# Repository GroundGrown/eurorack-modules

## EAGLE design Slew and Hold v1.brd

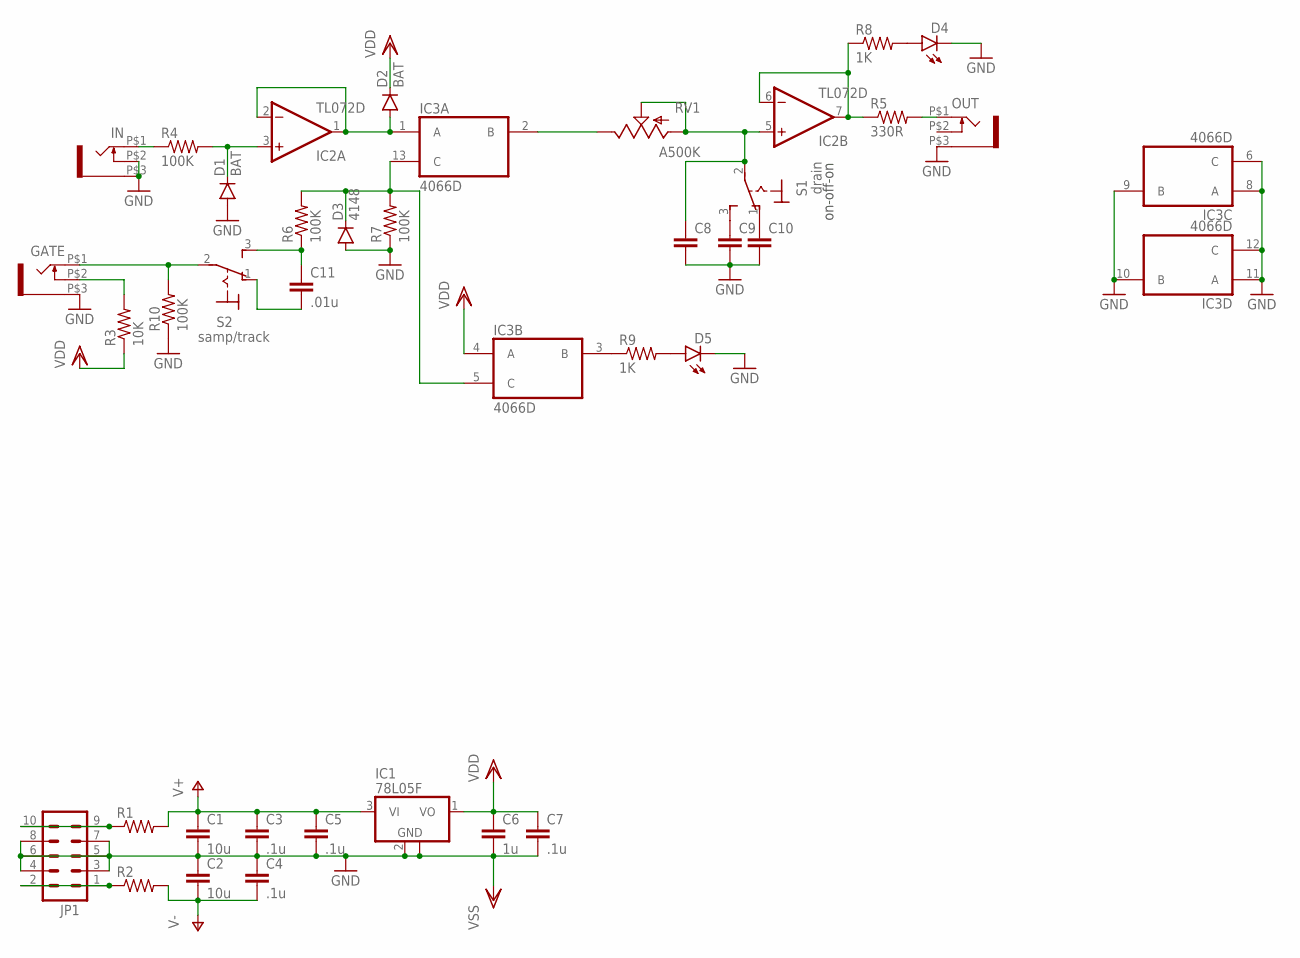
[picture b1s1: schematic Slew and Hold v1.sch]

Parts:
C1, C2: 10u; 1206
C3, C4, C5, C7: .1u; 0805
C6: 1u; 0805
C8, C9, C10: CAP0805; 0805
C11: .01u; 0805
D1, D2: BAT; SOD-123
D3: 4148; SOD-123
D4, D5: LED3MM
GATE: WQP-PJ301M-12_JACK
IC1: 78L05F; SOT89
IC2: TL072D; SO08
IC3: 4066D; SO14
IN: WQP-PJ301M-12_JACK
JP1: M05X2PTH; AVR_ICSP
OUT: WQP-PJ301M-12_JACK
R1, R2: RESISTOR0805-RES; 0805
R3: 10K; 0805
R4, R6, R7, R10: 100K; 0805
R5: 330R; 0805
R8, R9: 1K; 0805
RV1: A500K; ALPS_POT
S1: drain; M9040P
S2: samp/track; M9040P

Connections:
GND: C1.2, C2.1, C3.2, C4.1, C5.2, C6.2, C7.2, C8.2, C9.2, C10.2, D1.A, D3.A, D4.K (C), D5.K (C), GATE.P$3 (1), IC1.2 (GND), IC1.2@1 (GND), IC3.6 (C), IC3.7 (VSS), IC3.8 (A), IC3.9 (B), IC3.10 (B), IC3.11 (A), IC3.12 (C), IN.P$2 (3), IN.P$3 (1), JP1.3, JP1.4, JP1.5, JP1.6, JP1.7, JP1.8, OUT.P$3 (1), R7.1, R10.1
unnamed: JP1.9, JP1.10, R1.1
unnamed: JP1.1, JP1.2, R2.1
unnamed: D2.A, IC2.1 (OUT), IC2.2 (-IN), IC3.1 (A)
unnamed: D1.C, IC2.3 (+IN), R4.2
unnamed: IN.P$1 (2), R4.1
unnamed: IC3.2 (B), RV1.P$1 (E)
unnamed: C8.1, IC2.5 (+IN), RV1.P$2 (S), RV1.P$3 (A), S1.2
unnamed: C9.1, S1.3 (S)
unnamed: C10.1, S1.1 (O)
unnamed: D4.A, R8.2
unnamed: IC2.6 (-IN), IC2.7 (OUT), R5.1, R8.1
unnamed: GATE.P$1 (2), R10.2, S2.2
unnamed: D3.C, IC3.5 (C), IC3.13 (C), R6.2, R7.2
unnamed: GATE.P$2 (3), R3.2
unnamed: OUT.P$1 (2), R5.2
unnamed: C11.1, R6.1, S2.3 (S)
unnamed: C11.2, S2.1 (O)
unnamed: IC3.3 (B), R9.1
unnamed: D5.A, R9.2
V+: C1.1, C3.1, C5.1, IC1.3 (VI), IC2.8 (V+), R1.2
V-: C2.2, C4.2, IC2.4 (V-), R2.2
VDD: C6.1, C7.1, D2.C, IC1.1 (VO), IC3.4 (A), IC3.14 (VDD), R3.1

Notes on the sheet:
on-off-on

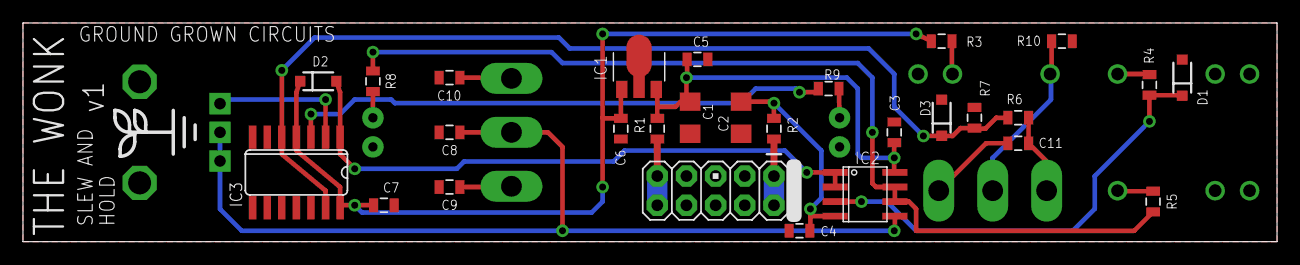
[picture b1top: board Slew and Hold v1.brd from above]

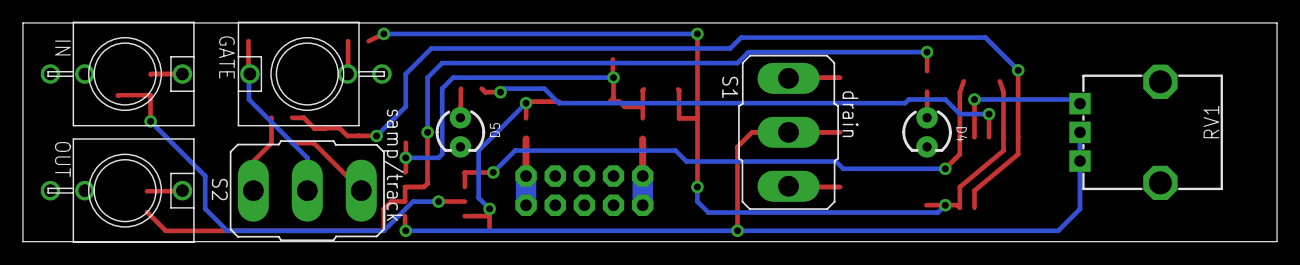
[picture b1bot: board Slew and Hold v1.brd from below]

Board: 2 copper layers, 109.2 x 19.1 mm, 37 parts (8 on the bottom side), 23 nets.

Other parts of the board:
U$1: LOGO_SMALL

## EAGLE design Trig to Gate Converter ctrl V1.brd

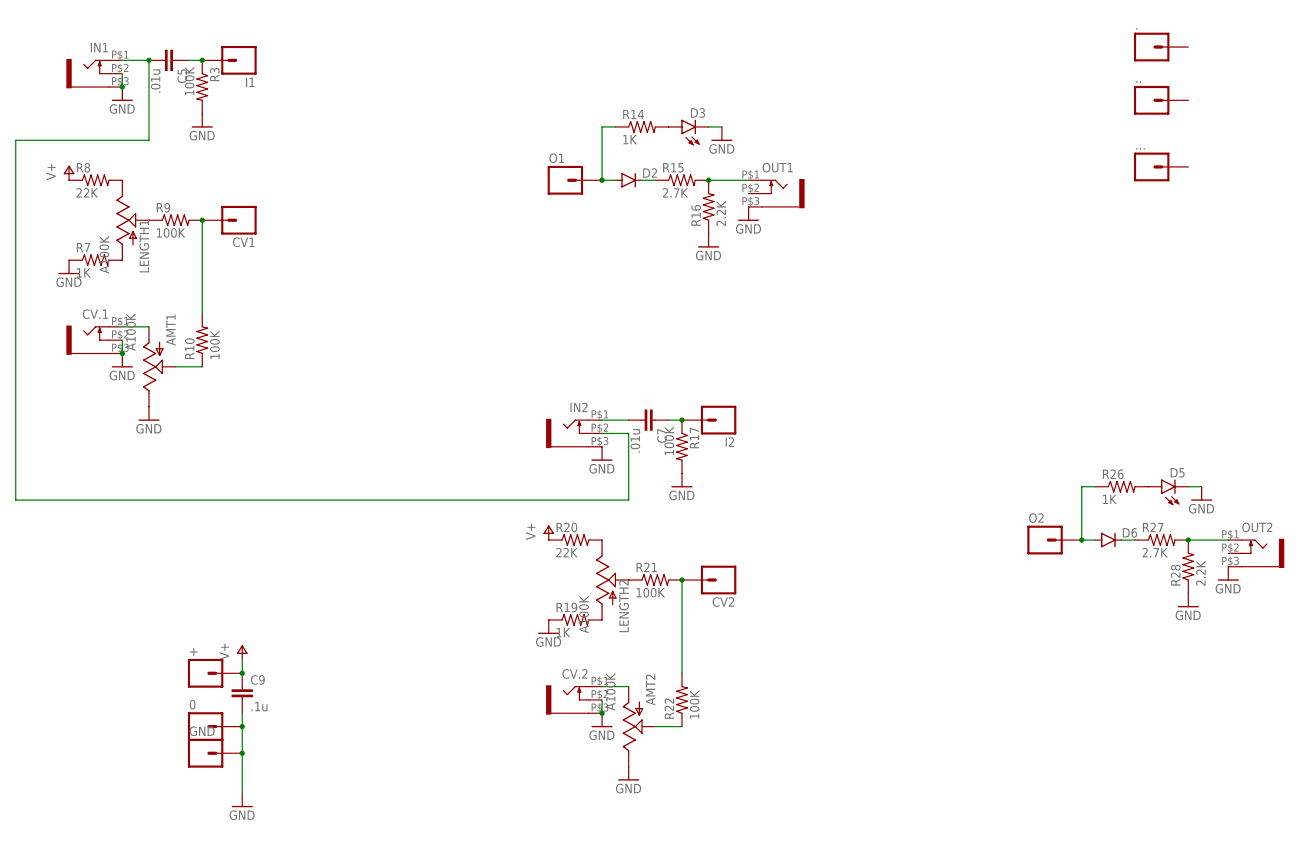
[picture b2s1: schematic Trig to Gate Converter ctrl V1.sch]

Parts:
0, ., .., ...: M01PTH; 1X01
+: M01PTH; 1X01
AMT1, AMT2: A100K; ALPS_POT
C5, C7: .01u; 0805
C9: .1u; 0805
CV1, CV2: M01PTH; 1X01
CV.1, CV.2: WQP-PJ301M-12_JACK
D2, D6: DIODESOD123; SOD-123
D3, D5: LED3MM
GND: M01PTH; 1X01
I1, I2: M01PTH; 1X01
IN1, IN2: WQP-PJ301M-12_JACK
LENGTH1, LENGTH2: A100K; ALPS_POT
O1, O2: M01PTH; 1X01
OUT1, OUT2: WQP-PJ301M-12_JACK
R3, R9, R10, R17, R21, R22: 100K; 0805
R7, R14, R19, R26: 1K; 0805
R8, R20: 22K; 0805
R15, R27: 2.7K; 0805
R16, R28: 2.2K; 0805

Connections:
GND: 0.1, AMT1.P$1 (E), AMT2.P$1 (E), C9.2, CV.1.P$2 (3), CV.1.P$3 (1), CV.2.P$2 (3), CV.2.P$3 (1), D3.K (C), D5.K (C), GND.1, IN1.P$2 (3), IN1.P$3 (1), IN2.P$3 (1), OUT1.P$3 (1), OUT2.P$3 (1), R3.2, R7.1, R16.1, R17.2, R19.1, R28.1
unnamed: LENGTH2.P$1 (E), R20.2
unnamed: LENGTH1.P$3 (A), R7.2
unnamed: LENGTH1.P$1 (E), R8.2
unnamed: LENGTH1.P$2 (S), R9.1
unnamed: AMT1.P$3 (A), CV.1.P$1 (2)
unnamed: AMT1.P$2 (S), R10.1
unnamed: CV1.1, R9.2, R10.2
unnamed: C5.2, IN1.P$1 (2), IN2.P$2 (3)
unnamed: C5.1, I1.1, R3.1
unnamed: D3.A, R14.2
unnamed: OUT1.P$1 (2), R15.2, R16.2
unnamed: D2.C, R15.1
unnamed: D2.A, O1.1, R14.1
unnamed: LENGTH2.P$3 (A), R19.2
unnamed: LENGTH2.P$2 (S), R21.1
unnamed: AMT2.P$3 (A), CV.2.P$1 (2)
unnamed: AMT2.P$2 (S), R22.1
unnamed: CV2.1, R21.2, R22.2
unnamed: C7.2, IN2.P$1 (2)
unnamed: C7.1, I2.1, R17.1
unnamed: D5.A, R26.2
unnamed: OUT2.P$1 (2), R27.2, R28.2
unnamed: D6.C, R27.1
unnamed: D6.A, O2.1, R26.1
V+: +.1, C9.1, R8.1, R20.1

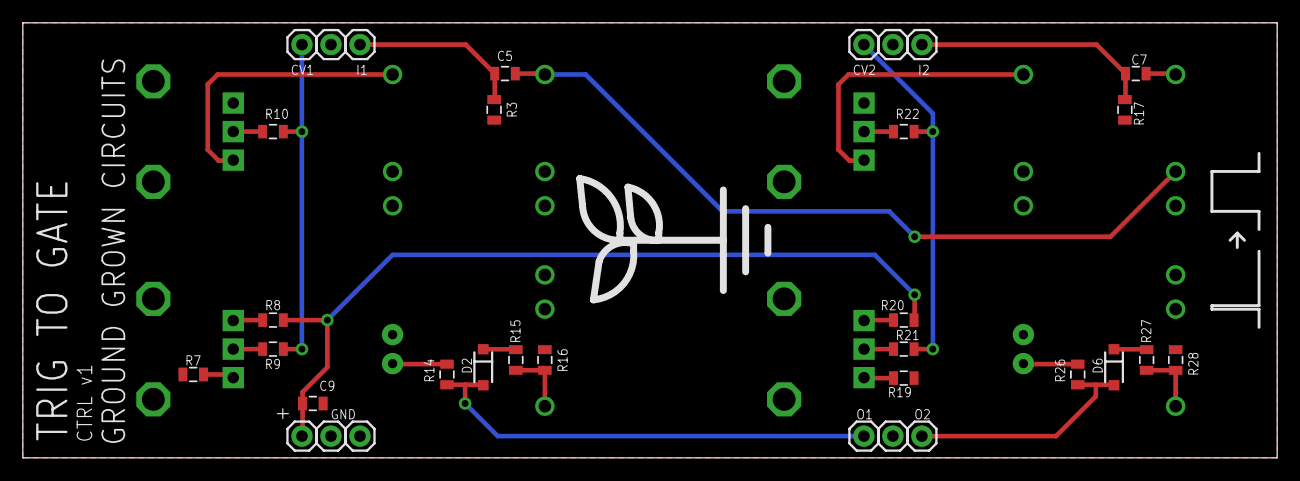
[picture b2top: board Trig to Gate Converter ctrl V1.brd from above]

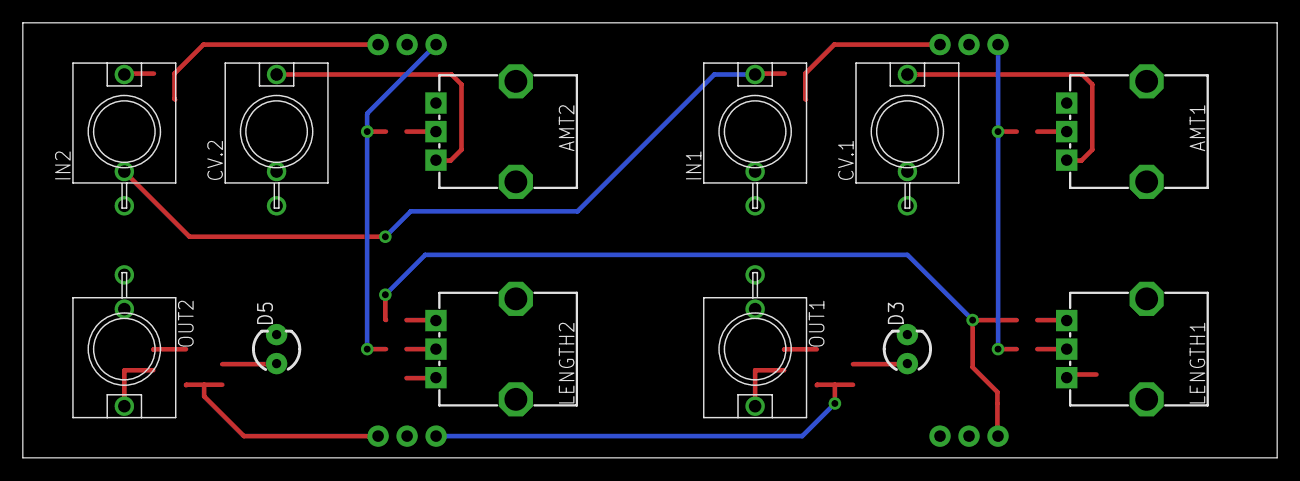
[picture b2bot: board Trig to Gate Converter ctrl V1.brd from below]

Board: 2 copper layers, 109.9 x 38.1 mm, 46 parts (12 on the bottom side), 26 nets.

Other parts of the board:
U$1: LOGO_LARGE

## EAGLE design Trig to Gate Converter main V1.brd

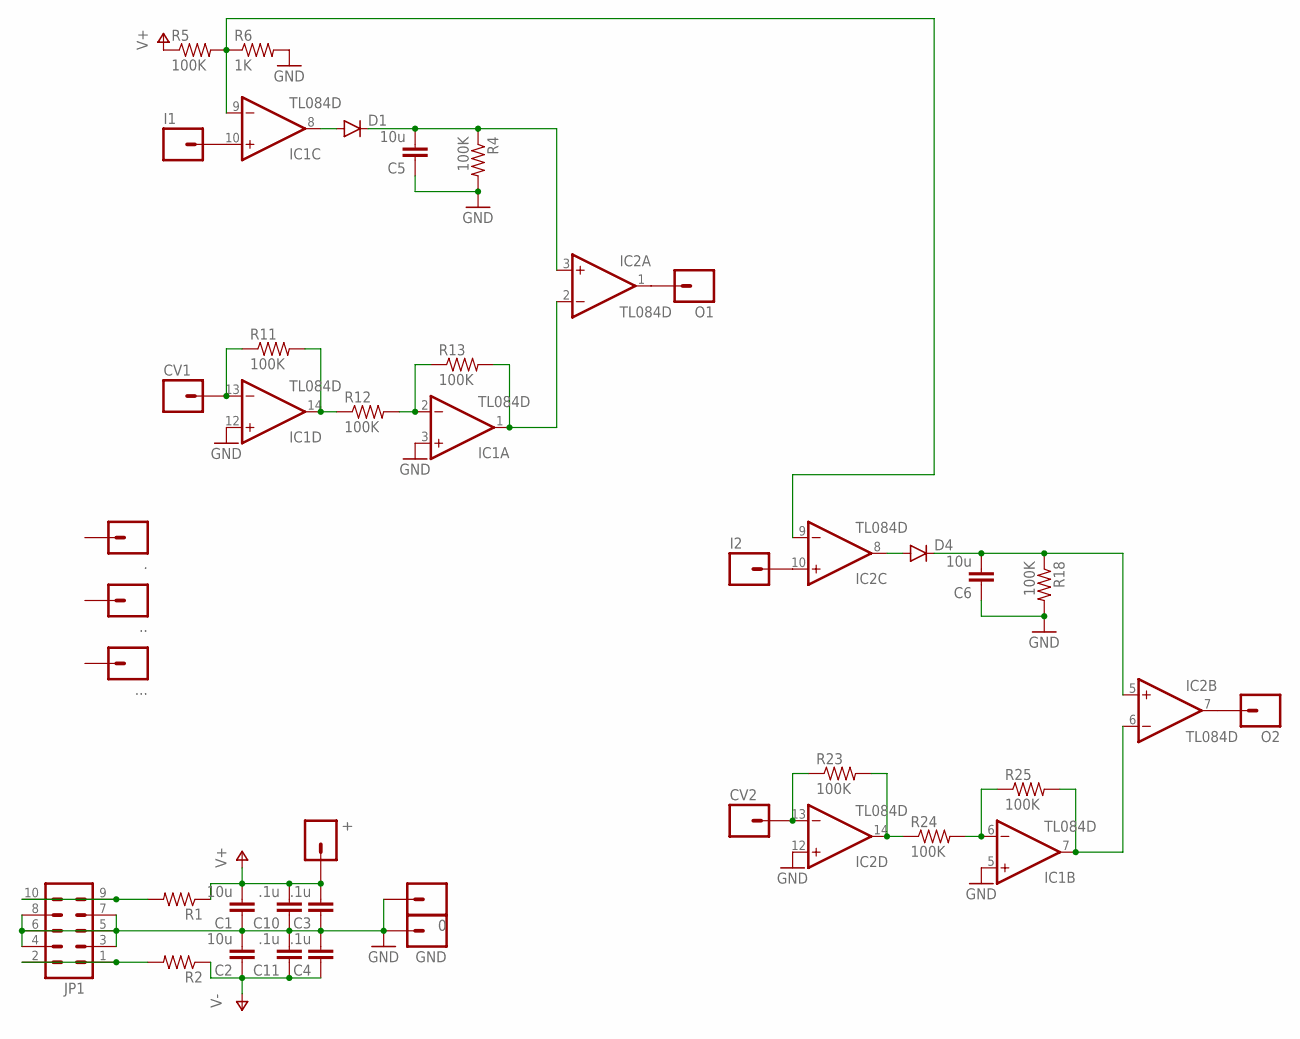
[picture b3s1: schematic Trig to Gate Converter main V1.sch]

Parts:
0, ., .., ...: M01PTH; 1X01
+: M01PTH; 1X01
C1, C2, C5, C6: 10u; 1206
C3, C4, C10, C11: .1u; 0805
CV1, CV2: M01PTH; 1X01
D1, D4: DIODESOD123; SOD-123
GND: M01PTH; 1X01
I1, I2: M01PTH; 1X01
IC1, IC2: TL084D; SO14
JP1: M05X2PTH; AVR_ICSP
O1, O2: M01PTH; 1X01
R1, R2: RESISTOR0805-RES; 0805
R4, R5, R11, R12, R13, R18, R23, R24, R25: 100K; 0805
R6: 1K; 0805

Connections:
GND: 0.1, C1.1, C2.2, C3.1, C4.2, C5.1, C6.1, C10.1, C11.2, GND.1, IC1.3 (+IN), IC1.5 (+IN), IC1.12 (+IN), IC2.12 (+IN), JP1.3, JP1.4, JP1.5, JP1.6, JP1.7, JP1.8, R4.2, R6.2, R18.2
unnamed: I1.1, IC1.10 (+IN)
unnamed: I2.1, IC2.10 (+IN)
unnamed: IC1.9 (-IN), IC2.9 (-IN), R5.2, R6.1
unnamed: IC2.1 (OUT), O1.1
unnamed: IC2.7 (OUT), O2.1
unnamed: CV1.1, IC1.13 (-IN), R11.1
unnamed: D1.A, IC1.8 (OUT)
unnamed: C5.2, D1.C, IC2.3 (+IN), R4.1
unnamed: IC1.14 (OUT), R11.2, R12.1
unnamed: IC1.2 (-IN), R12.2, R13.1
unnamed: IC1.1 (OUT), IC2.2 (-IN), R13.2
unnamed: JP1.9, JP1.10, R1.2
unnamed: JP1.1, JP1.2, R2.2
unnamed: CV2.1, IC2.13 (-IN), R23.1
unnamed: D4.A, IC2.8 (OUT)
unnamed: C6.2, D4.C, IC2.5 (+IN), R18.1
unnamed: IC2.14 (OUT), R23.2, R24.1
unnamed: IC1.6 (-IN), R24.2, R25.1
unnamed: IC1.7 (OUT), IC2.6 (-IN), R25.2
V+: +.1, C1.2, C3.2, C10.2, IC1.4 (V+), IC2.4 (V+), R1.1, R5.1
V-: C2.1, C4.1, C11.1, IC1.11 (V-), IC2.11 (V-), R2.1

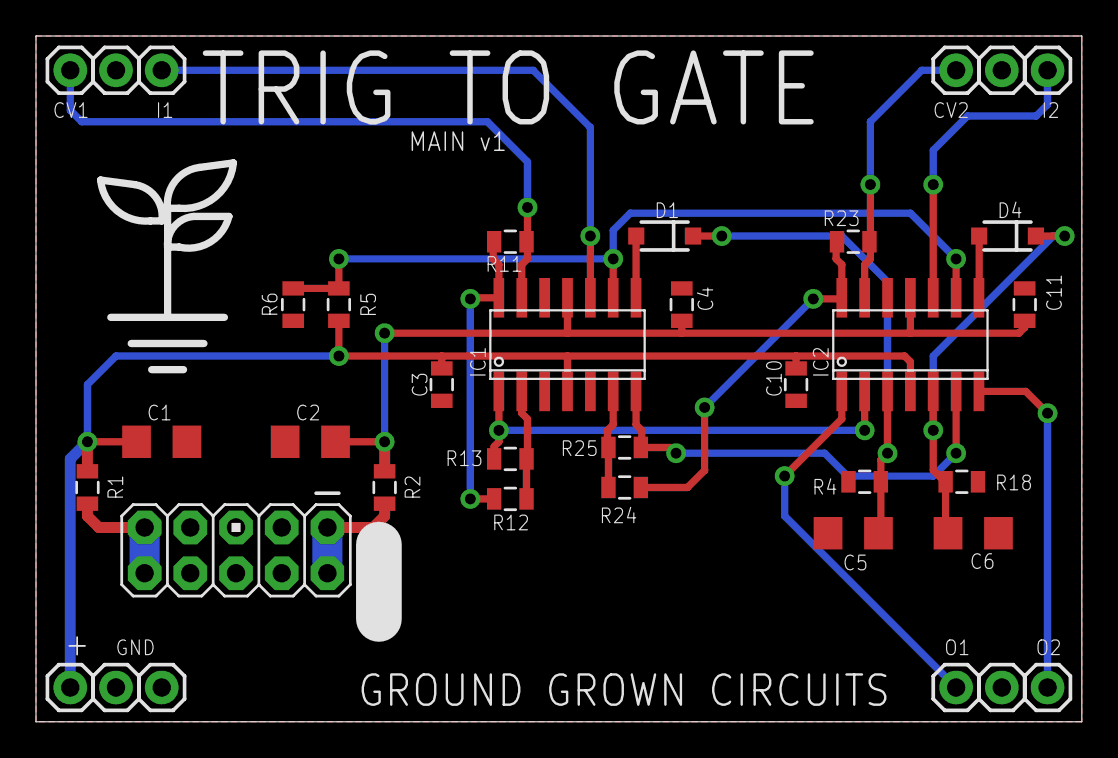
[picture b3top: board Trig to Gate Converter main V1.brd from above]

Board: 2 copper layers, 58.1 x 38.1 mm, 38 parts (0 on the bottom side), 22 nets.

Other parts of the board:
U$1: LOGO_MED

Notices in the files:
parts and their libraries:
SparkFun-Capacitors: Licensing: Creative Commons ShareAlike 4.0 International - https://creativecommons.org/licenses/by-sa/4.0
